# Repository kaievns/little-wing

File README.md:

# Little Wing Keyboard

This my attempt to build a better keyboard for myself.

Think of it as a 32% split bluetooth keyboard merged with the classic MX Ergo trackball

## License

Little Wing Keyboard © 2024 by Kai Evans is licensed under CC BY-SA 4.0

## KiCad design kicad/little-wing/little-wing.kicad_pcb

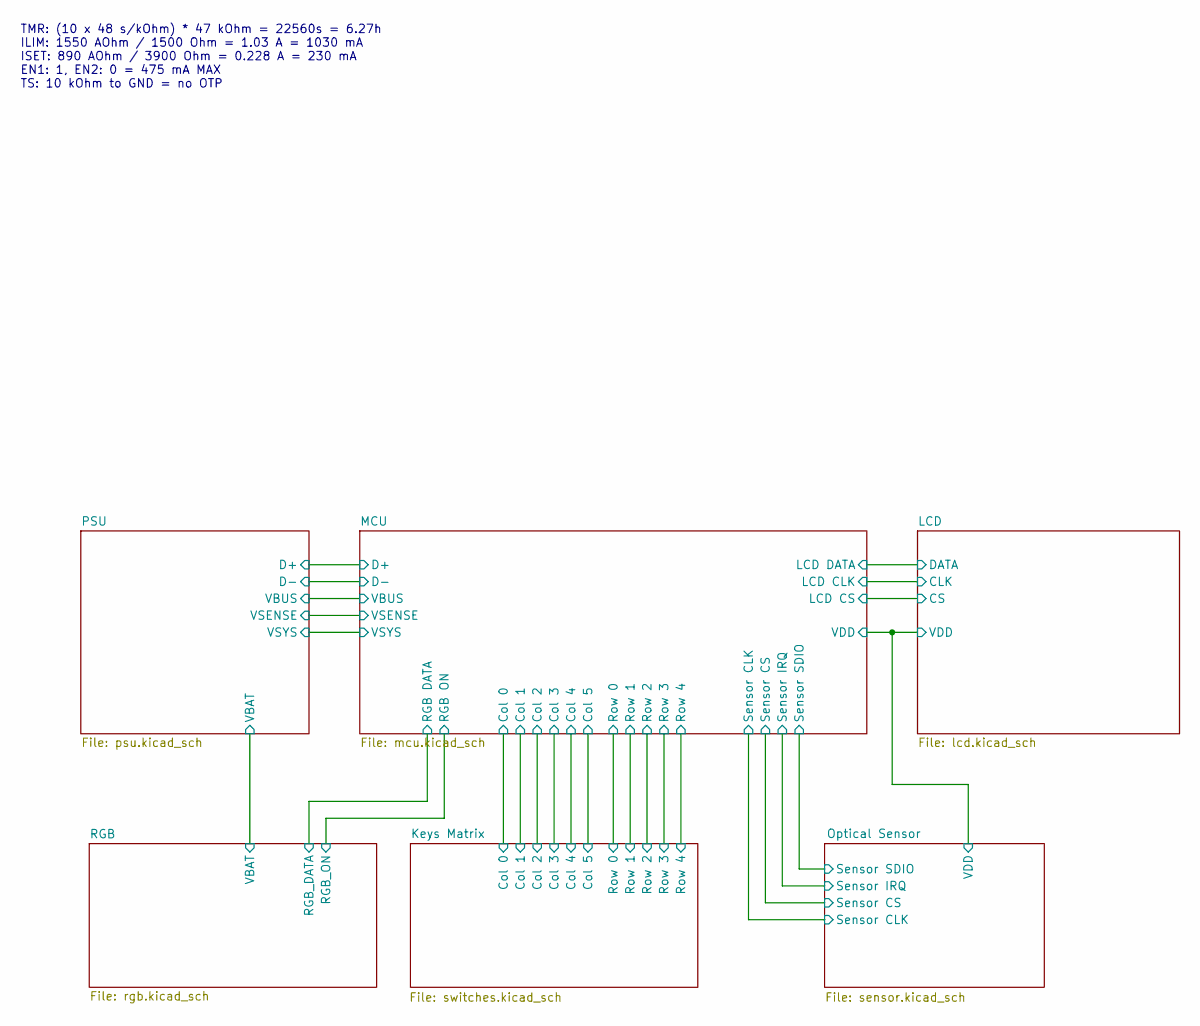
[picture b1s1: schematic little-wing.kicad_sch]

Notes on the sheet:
TMR: (10 x 48 s/kOhm) * 47 kOhm = 22560s = 6.27h ILIM: 1550 AOhm / 1500 Ohm = 1.03 A = 1030 mA ISET: 890 AOhm / 3900 Ohm = 0.228 A = 230 mA EN1: 1, EN2: 0 = 475 mA MAX TS: 10 kOhm to GND = no OTP

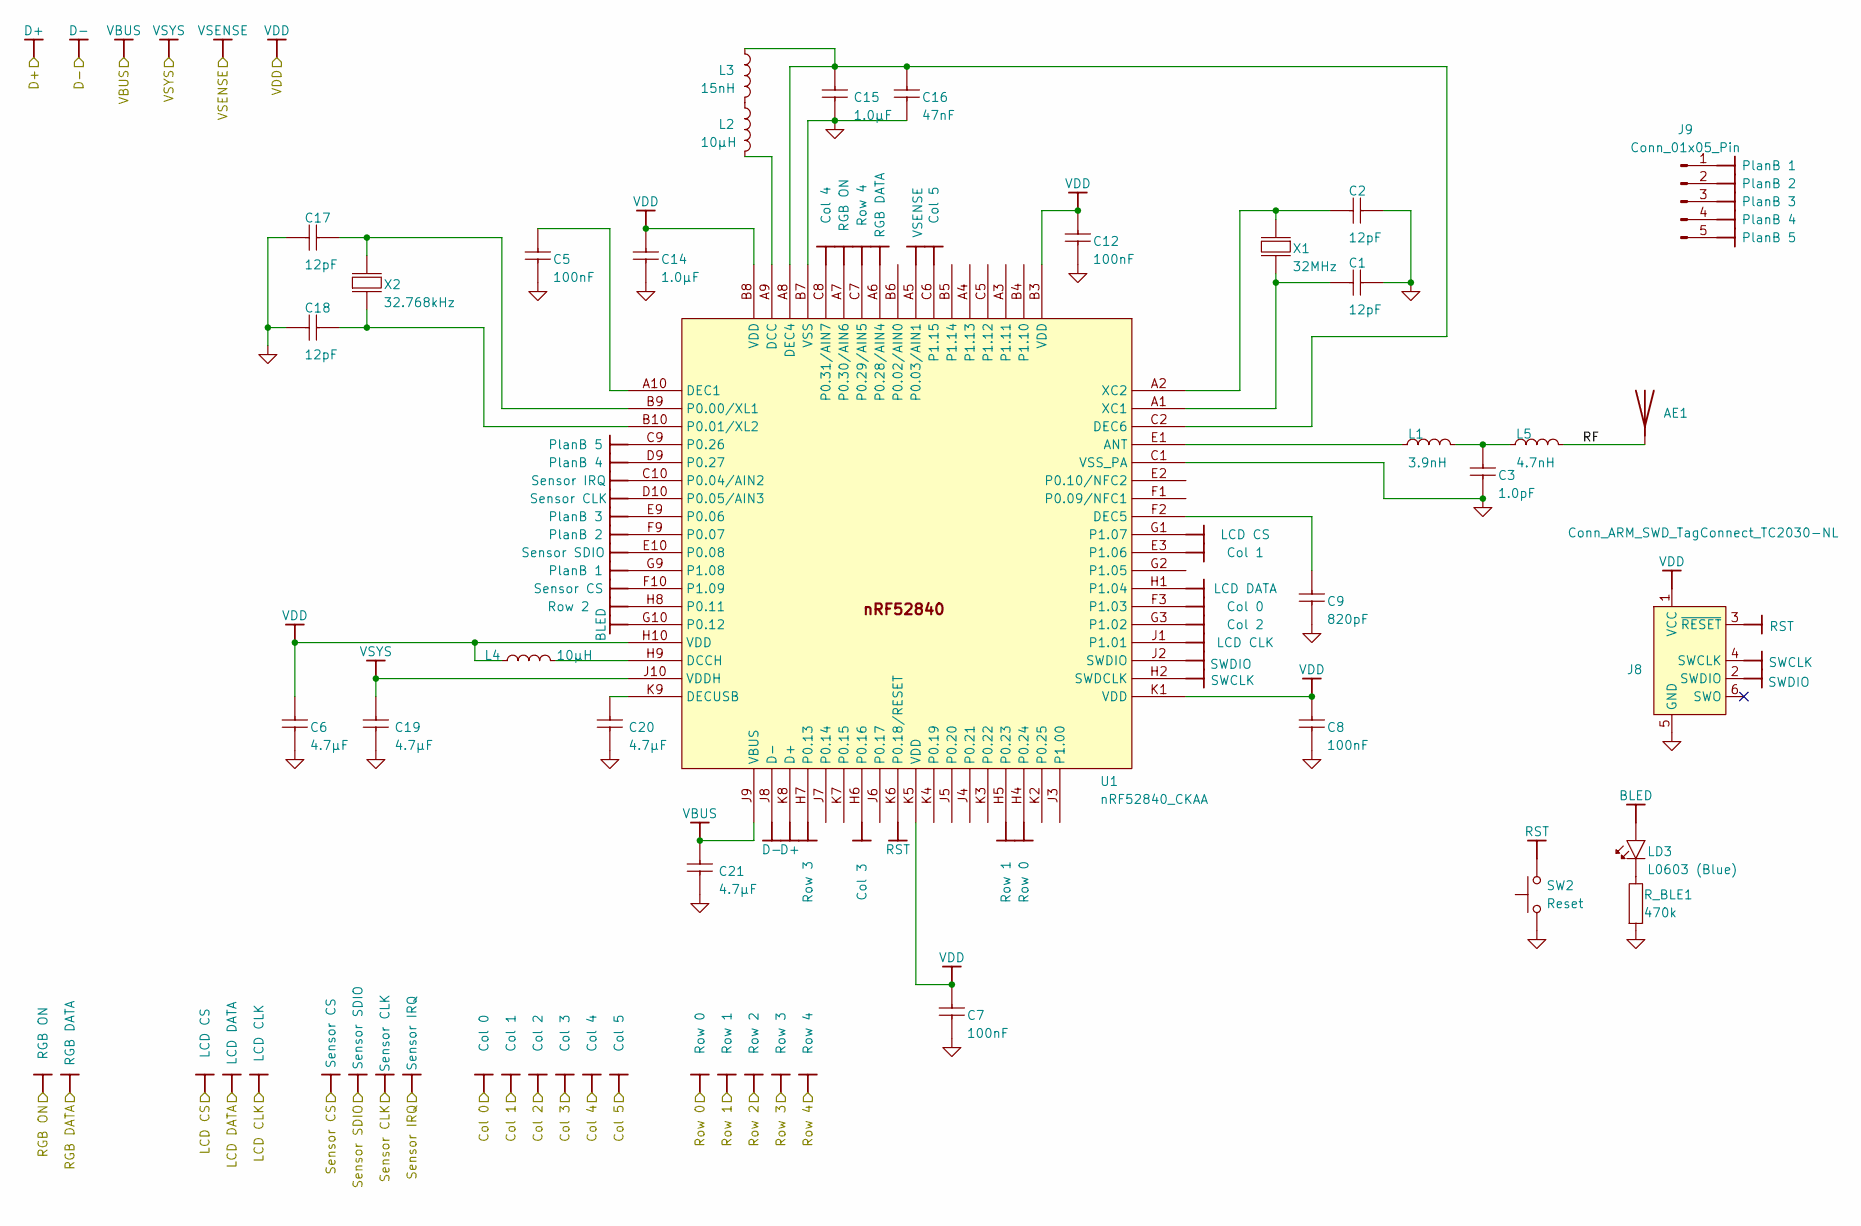
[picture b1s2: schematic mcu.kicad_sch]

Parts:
AE1: 2450AT18A100E; ANT2012LL13R2400A; PARTREV 1.3
C1, C2, C17, C18: 12pF; C_0201_0603Metric; PART NUMBER C0201-12p
C3: 1.0pF; C_0201_0603Metric; PART NUMBER C0201-1.0p
C5, C7, C8: 100nF; C_0201_0603Metric; PART NUMBER C0201-100n
C6, C20: 4.7µF; CAPC1608X06L; PART NUMBER C0603-4µ7-6.3V-X7R
C9: 820pF; C_0201_0603Metric; PART NUMBER C0201-820p
C12: 100nF; CAPC0603X03L_C; PART NUMBER C0201-100n
C14, C15: 1.0µF; CAPC1608X06L; PART NUMBER C0603-1µ0
C16: 47nF; CAPC0603X03L_C; PART NUMBER C0201-47n
C19, C21: 4.7µF; CAPC1608X06L; PART NUMBER C0603-4µ7-10V-X7S
J8: Conn_ARM_SWD_TagConnect_TC2030-NL; Tag-Connect_TC2030-IDC-NL_2x03_P1.27mm_Vertical
J9: Conn_01x05_Pin; JST_SHL_SM05B-SHLS-TF_1x05-1MP_P1.00mm_Horizontal
L1: 3.9nH; INDC0603X03L_C; PART NUMBER L0201-3n9
L2, L4: 10µH; INDC1608X06L; PART NUMBER L0603-10µ
L3: 15nH; INDC1005X04L; PART NUMBER L0402-15n
L5: 4.7nH; INDC0603X03L_C; PART NUMBER L0201-4n7
LD3: L0603 (Blue); LED_0201_0603Metric
R_BLE1: 470k; R_0201_0603Metric
SW2: Reset; SW_SPST_B3U-3000P
U1: nRF52840_CKAA; BGA94C35P10X10_352X356X50; PART NUMBER nRF52840-CKAAD0
X1: 32MHz; Crystal_SMD_1210-4Pin_1.2x1.0mm; PART NUMBER XTAL_SMD2016_32MHz_8pF_General
X2: 32.768kHz; XTAL_ECS32761210TR; PART NUMBER XTAL_SMD2012_32.768kHz_9pF_General

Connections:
/MCU/RF: AE1.1 (A), L5.2
BLED: LD3.2 (A), U1.G10 (P0.12)
Col 0: U1.F3 (P1.03); also elsewhere on the board
Col 1: U1.E3 (P1.06); also elsewhere on the board
Col 2: U1.G3 (P1.02); also elsewhere on the board
Col 3: U1.H6 (P0.16); also elsewhere on the board
Col 4: U1.C8 (P0.31/AIN7); also elsewhere on the board
Col 5: U1.C6 (P1.15); also elsewhere on the board
D+: U1.K8 (D+); also elsewhere on the board
D-: U1.J8 (D-); also elsewhere on the board
LCD CLK: U1.J1 (P1.01); also elsewhere on the board
LCD CS: U1.G1 (P1.07); also elsewhere on the board
LCD DATA: U1.H1 (P1.04); also elsewhere on the board
unnamed: C3.2, L1.2, L5.1
unnamed: L2.1, L3.2
unnamed: LD3.1 (C), R_BLE1.1
unnamed: L1.1, U1.E1 (ANT)
unnamed: L2.2, U1.A9 (DCC)
unnamed: L4.2, U1.H9 (DCCH)
unnamed: C5.1, U1.A10 (DEC1)
unnamed: C15.2, C16.1, L3.1, U1.A8 (DEC4), U1.C2 (DEC6)
unnamed: C9.1, U1.F2 (DEC5)
unnamed: C20.1, U1.K9 (DECUSB)
unnamed: C17.1, U1.B9 (P0.00/XL1), X2.1 (inp)
unnamed: C18.1, U1.B10 (P0.01/XL2), X2.2 (out)
unnamed: C1.1, U1.A1 (XC1), X1.1 (inp)
unnamed: C2.1, U1.A2 (XC2), X1.3 (out)
PlanB 1: J9.1, U1.G9 (P1.08)
PlanB 2: J9.2, U1.F9 (P0.07)
PlanB 3: J9.3, U1.E9 (P0.06)
PlanB 4: J9.4, U1.D9 (P0.27)
PlanB 5: J9.5, U1.C9 (P0.26)
RGB DATA: U1.A6 (P0.28/AIN4); also elsewhere on the board
RGB ON: U1.A7 (P0.30/AIN6); also elsewhere on the board
RST: J8.3 (~RESET), SW2.2, U1.K6 (P0.18/RESET); also elsewhere on the board
Row 0: U1.H4 (P0.24); also elsewhere on the board
Row 1: U1.H5 (P0.23); also elsewhere on the board
Row 2: U1.H8 (P0.11); also elsewhere on the board
Row 3: U1.H7 (P0.13); also elsewhere on the board
Row 4: U1.C7 (P0.29/AIN5); also elsewhere on the board
SWCLK: J8.4 (SWCLK), U1.H2 (SWDCLK)
SWDIO: J8.2 (SWDIO), U1.J2 (SWDIO)
Sensor CLK: U1.D10 (P0.05/AIN3); also elsewhere on the board
Sensor CS: U1.F10 (P1.09); also elsewhere on the board
Sensor IRQ: U1.C10 (P0.04/AIN2); also elsewhere on the board
Sensor SDIO: U1.E10 (P0.08); also elsewhere on the board
VBUS: C21.1, U1.J9 (VBUS); also elsewhere on the board
VDD: C6.1, C7.1, C8.1, C12.1, C14.1, J8.1 (VCC), L4.1, U1.B3 (VDD), U1.B8 (VDD), U1.H10 (VDD), U1.K1 (VDD), U1.K5 (VDD); also elsewhere on the board
VSENSE: U1.A5 (P0.03/AIN1); also elsewhere on the board
VSYS: C19.1, U1.J10 (VDDH); also elsewhere on the board

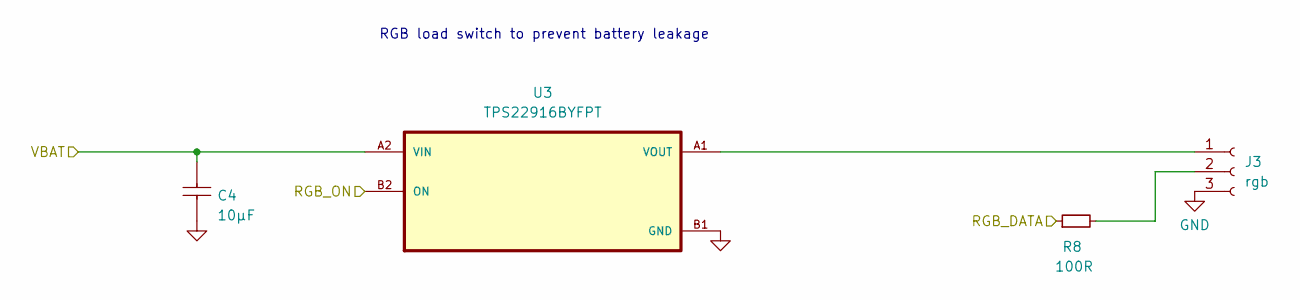
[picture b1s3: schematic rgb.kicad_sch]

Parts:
C4: 10µF; CAPC1608X06L; PART NUMBER C0603-1µ0
J3: rgb; JST_SH_SM03B-SRSS-TB_1x03-1MP_P1.00mm_Horizontal
R8: 100R; R_0201_0603Metric
U3: TPS22916BYFPT; BGA4C40P2X2_77X77X50

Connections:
unnamed: J3.1, U3.A1 (VOUT)
unnamed: J3.2, R8.2
RGB DATA: R8.1; also elsewhere on the board
RGB ON: U3.B2 (ON); also elsewhere on the board
VBAT: C4.2, U3.A2 (VIN); also elsewhere on the board

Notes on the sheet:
RGB load switch to prevent battery leakage

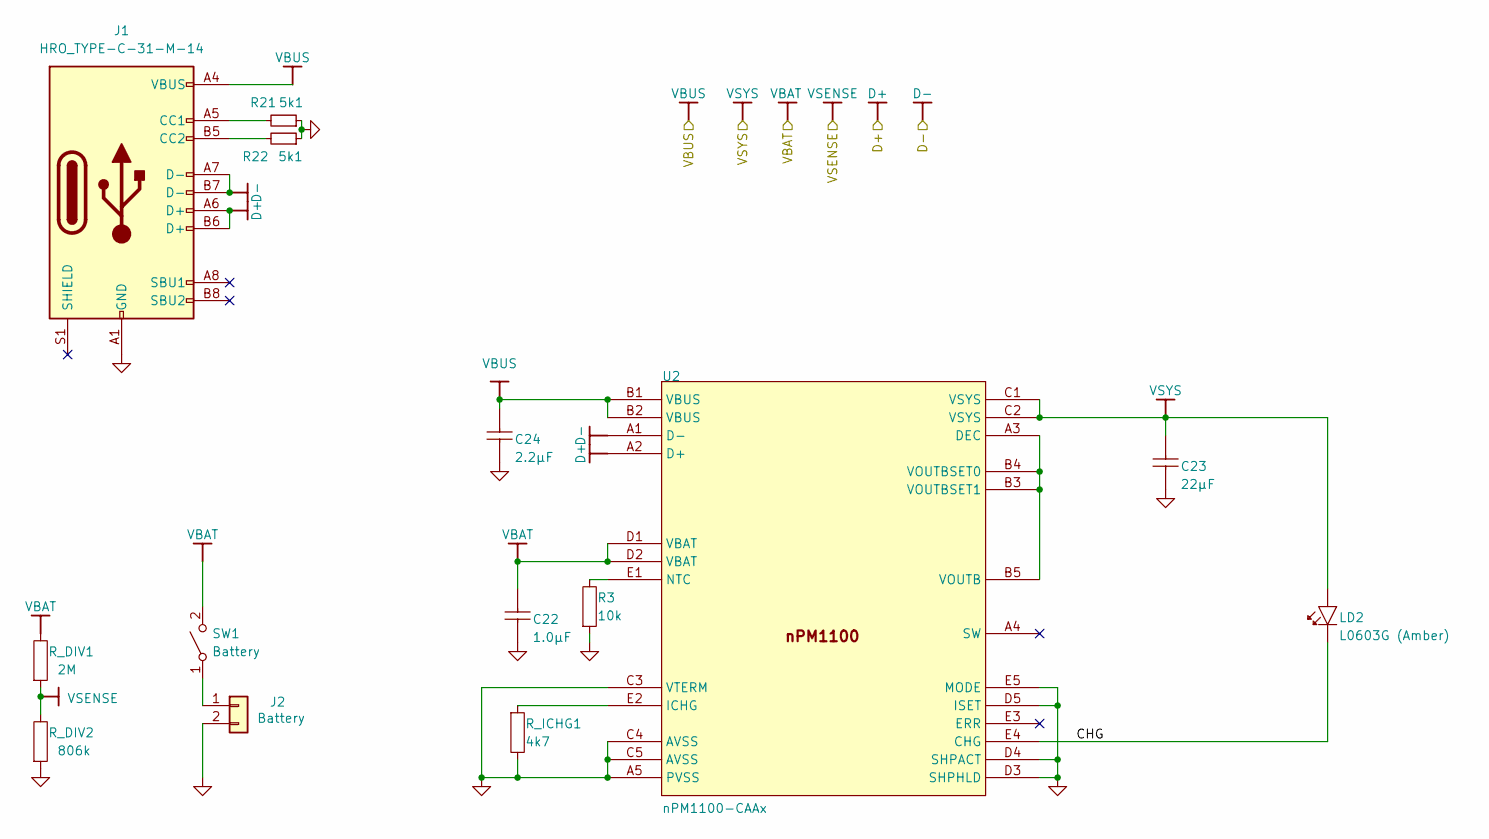
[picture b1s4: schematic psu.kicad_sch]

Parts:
C22: 1.0µF; C_0201_0603Metric
C23: 22µF; CAPC1608X06L
C24: 2.2µF; CAPC1608X06L
J1: HRO_TYPE-C-31-M-14; USB_C_Receptacle_HRO_TYPE-C-31-M-12
J2: Battery; JST_SH_SM02B-SRSS-TB_1x02-1MP_P1.00mm_Horizontal
LD2: L0603G (Amber); LED_0201_0603Metric
R3: 10k; R_0201_0603Metric
R21, R22: 5k1; R_0201_0603Metric
R_DIV1: 2M; R_0201_0603Metric
R_DIV2: 806k; R_0201_0603Metric
R_ICHG1: 4k7; R_0201_0603Metric
SW1: Battery; Switch_MSK12C02
U2: nPM1100-CAAx; BGA25C40P5X5_200X200X50

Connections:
/PSU/CHG: LD2.1 (C), U2.E4 (CHG)
D+: J1.A6 (D+), J1.B6 (D+), U2.A2 (D+); also elsewhere on the board
D-: J1.A7 (D-), J1.B7 (D-), U2.A1 (D-); also elsewhere on the board
unnamed: J1.A5 (CC1), R21.2
unnamed: J1.B5 (CC2), R22.2
unnamed 20: J2.1, SW1.1 (A); also elsewhere on the board
unnamed: U2.A3 (DEC), U2.B3 (VOUTBSET1), U2.B4 (VOUTBSET0), U2.B5 (VOUTB)
unnamed: R_ICHG1.2, U2.E2 (ICHG)
unnamed: R3.1, U2.E1 (NTC)
VBAT: C22.2, R_DIV1.1, SW1.2 (B), U2.D1 (VBAT), U2.D2 (VBAT); also elsewhere on the board
VBUS: C24.2, J1.A4 (VBUS), J1.A9 (VBUS), J1.B4 (VBUS), J1.B9 (VBUS), U2.B1 (VBUS), U2.B2 (VBUS); also elsewhere on the board
VSENSE: R_DIV1.2, R_DIV2.1; also elsewhere on the board
VSYS: C23.2, LD2.2 (A), U2.C1 (VSYS), U2.C2 (VSYS); also elsewhere on the board

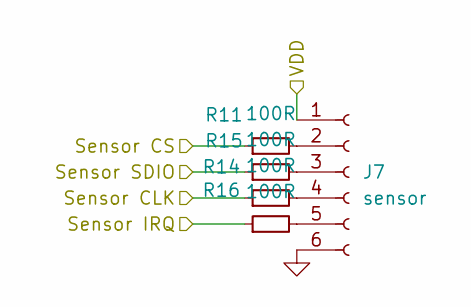
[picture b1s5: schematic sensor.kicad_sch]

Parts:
J7: sensor; JST_SH_SM06B-SRSS-TB_1x06-1MP_P1.00mm_Horizontal
R11, R14, R15, R16: 100R; R_0201_0603Metric

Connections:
unnamed: J7.2, R11.2
unnamed: J7.3, R14.2
unnamed: J7.4, R15.2
unnamed: J7.5, R16.2
Sensor CLK: R15.1; also elsewhere on the board
Sensor CS: R11.1; also elsewhere on the board
Sensor IRQ: R16.1; also elsewhere on the board
Sensor SDIO: R14.1; also elsewhere on the board
VDD: J7.1; also elsewhere on the board

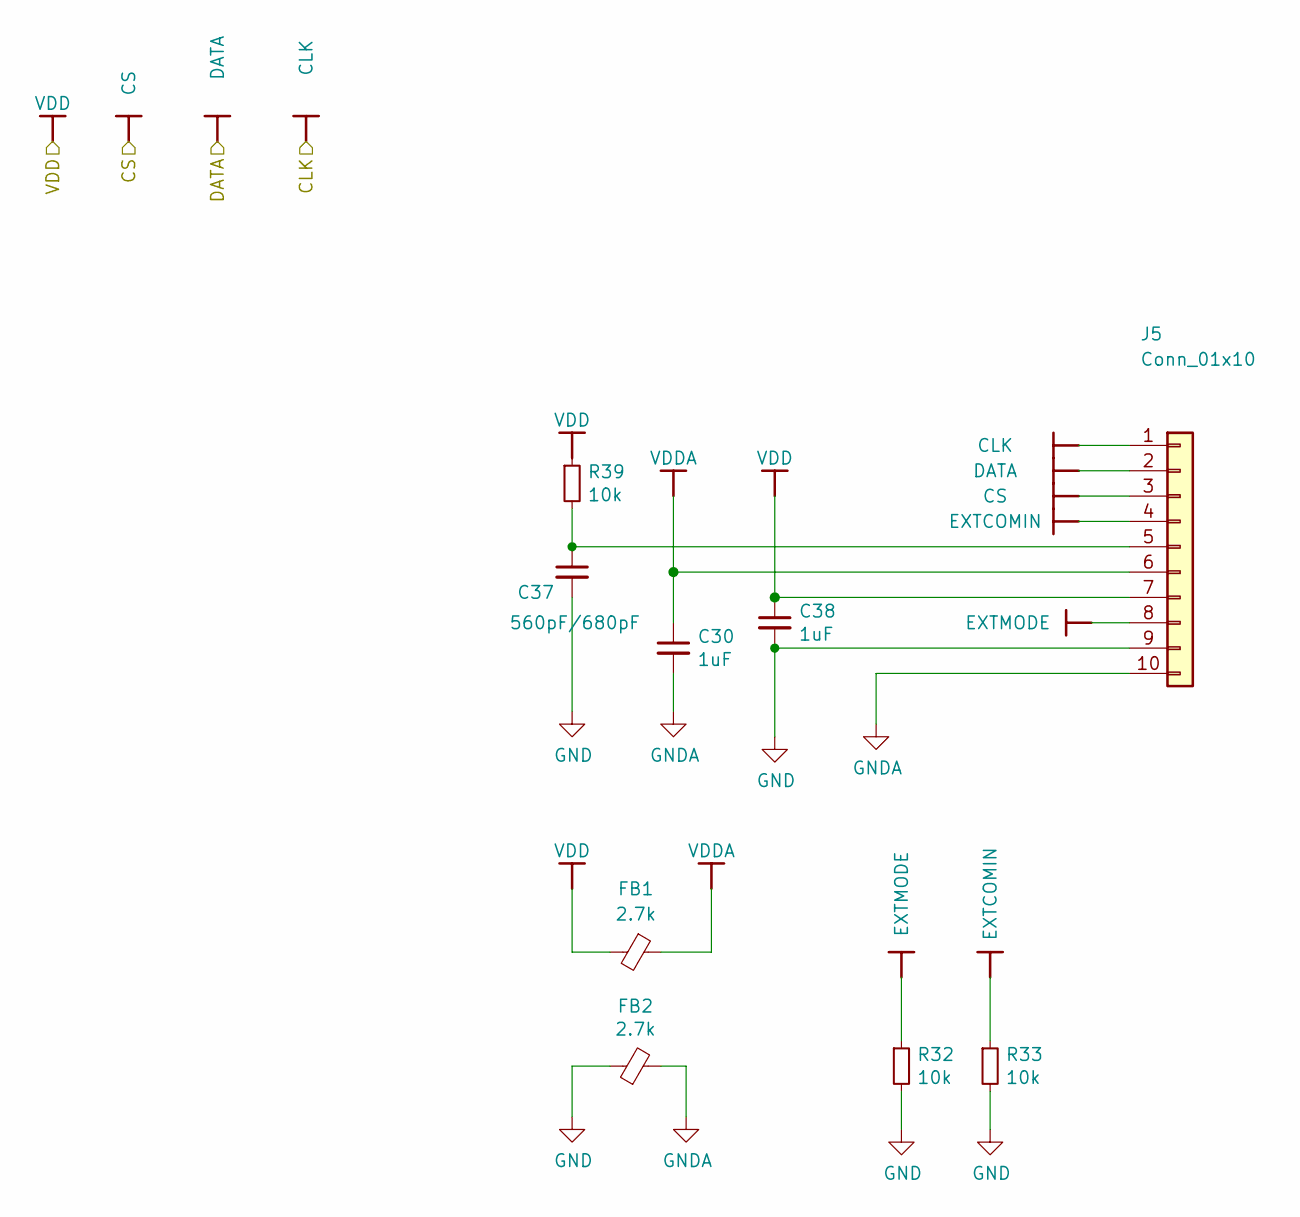
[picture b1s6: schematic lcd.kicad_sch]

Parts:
C30, C38: 1uF; C_0201_0603Metric; LCSC C15849
C37: 560pF/680pF; C_0201_0603Metric; LCSC C84721
FB1, FB2: 2.7k; R_0402_1005Metric; LCSC C1017
J5: Conn_01x10; CONN10x1_FH34SRJ-10S-0.5SH50_HIR; LCSC C506791
R32, R33, R39: 10k; R_0201_0603Metric; LCSC C25804

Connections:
EXTCOMIN: J5.4, R33.1
EXTMODE: J5.8, R32.1
GNDA: C30.2, FB2.2, J5.10
LCD CLK: J5.1; also elsewhere on the board
LCD CS: J5.3; also elsewhere on the board
LCD DATA: J5.2; also elsewhere on the board
unnamed: C37.1, J5.5, R39.2
VDD: C38.1, FB1.2, J5.7, R39.1; also elsewhere on the board
VDDA: C30.1, FB1.1, J5.6

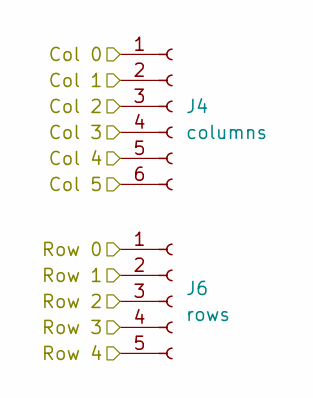
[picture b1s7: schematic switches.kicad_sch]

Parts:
J4: columns; JST_SH_SM06B-SRSS-TB_1x06-1MP_P1.00mm_Horizontal
J6: rows; JST_SH_SM05B-SRSS-TB_1x05-1MP_P1.00mm_Horizontal

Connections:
Col 0: J4.1; also elsewhere on the board
Col 1: J4.2; also elsewhere on the board
Col 2: J4.3; also elsewhere on the board
Col 3: J4.4; also elsewhere on the board
Col 4: J4.5; also elsewhere on the board
Col 5: J4.6; also elsewhere on the board
Row 0: J6.1; also elsewhere on the board
Row 1: J6.2; also elsewhere on the board
Row 2: J6.3; also elsewhere on the board
Row 3: J6.4; also elsewhere on the board
Row 4: J6.5; also elsewhere on the board

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
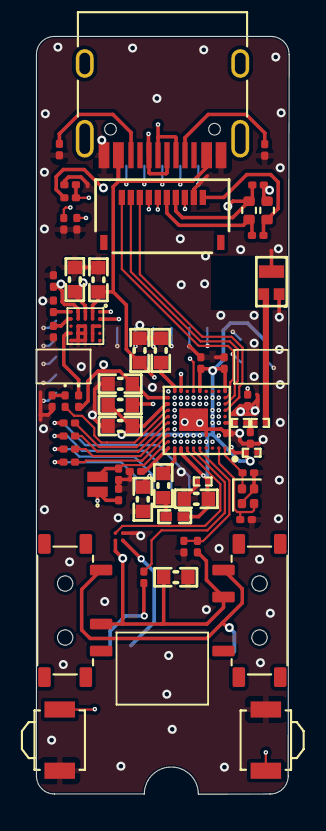
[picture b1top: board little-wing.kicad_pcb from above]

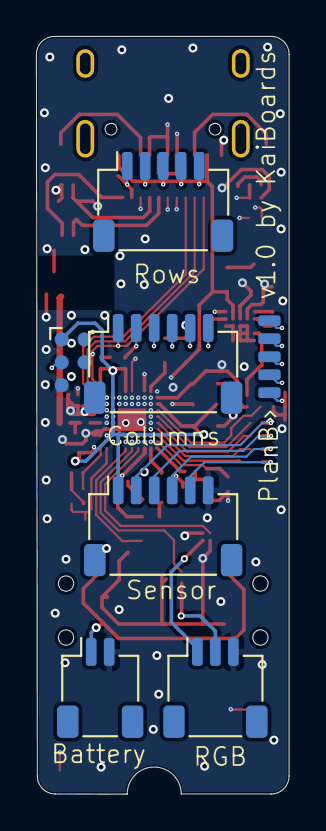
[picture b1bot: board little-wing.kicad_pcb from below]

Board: 4 copper layers, 14.0 x 42.1 mm, 67 parts (7 on the bottom side), 70 nets.

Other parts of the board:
SW1#2: Battery; Switch_MSK12C02
SW2#2: Reset; SW_SPST_B3U-3000P

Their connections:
unnamed 20: SW1#2.1 (A); also elsewhere on the board
RST: SW2#2.2; also elsewhere on the board
VBAT: SW1#2.2 (B); also elsewhere on the board

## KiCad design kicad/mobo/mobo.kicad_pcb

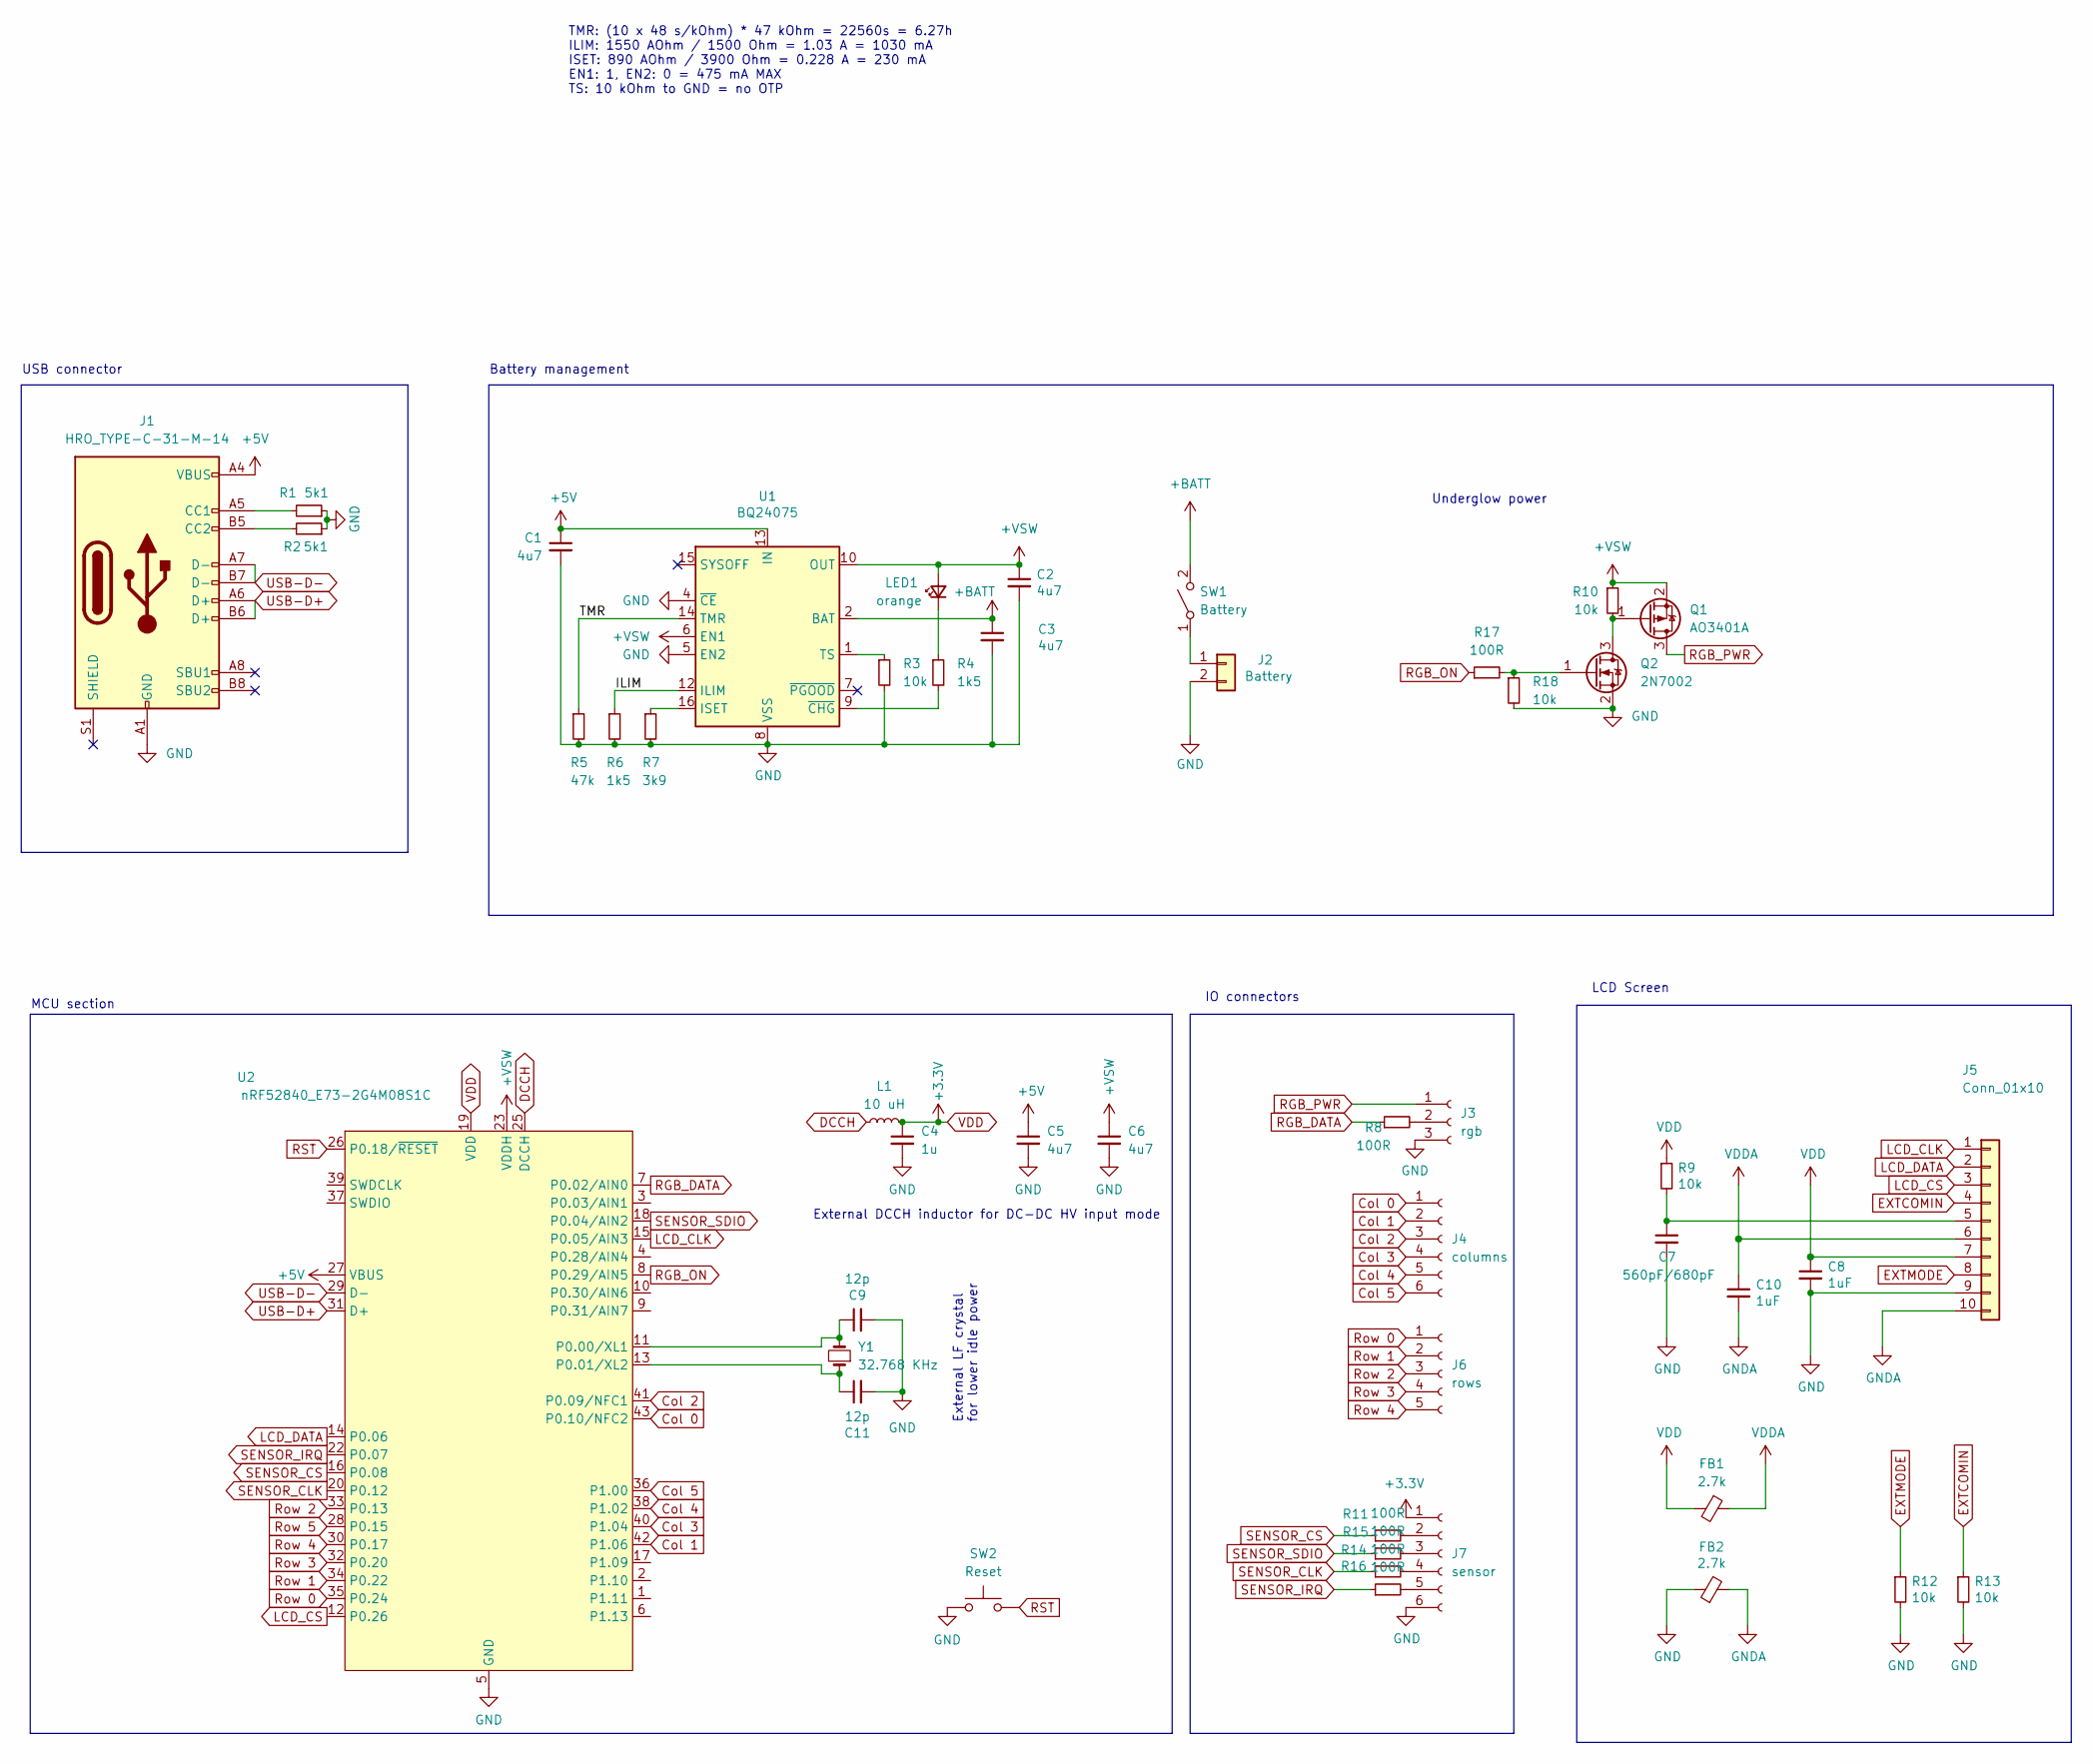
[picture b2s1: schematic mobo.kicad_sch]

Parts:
C1, C2, C3, C5, C6: 4u7; C_0402_1005Metric
C4: 1u; C_0402_1005Metric
C7: 560pF/680pF; C_0603_1608Metric_Pad1.08x0.95mm_HandSolder; LCSC C84721
C8, C10: 1uF; C_0603_1608Metric_Pad1.08x0.95mm_HandSolder; LCSC C15849
C9, C11: 12p; C_0402_1005Metric
FB1, FB2: 2.7k; R_0805_2012Metric_Pad1.20x1.40mm_HandSolder; LCSC C1017
J1: HRO_TYPE-C-31-M-14; USB_C_Receptacle_HRO_TYPE-C-31-M-12
J2: Battery; JST_SH_SM02B-SRSS-TB_1x02-1MP_P1.00mm_Horizontal
J3: rgb; JST_SH_SM03B-SRSS-TB_1x03-1MP_P1.00mm_Horizontal
J4: columns; JST_SH_SM06B-SRSS-TB_1x06-1MP_P1.00mm_Horizontal
J5: Conn_01x10; Hirose_FH12-10S-0.5SH_1x10-1MP_P0.50mm_Horizontal; LCSC C506791
J6: rows; JST_SH_SM05B-SRSS-TB_1x05-1MP_P1.00mm_Horizontal
J7: sensor; JST_SH_SM06B-SRSS-TB_1x06-1MP_P1.00mm_Horizontal
L1: 10 uH; L_0603_1608Metric; LCSC C92982
LED1: orange; LED_0402_1005Metric
Q1: AO3401A; SOT-23
Q2: 2N7002; SOT-23
R1, R2: 5k1; R_0402_1005Metric
R3, R10, R18: 10k; R_0402_1005Metric
R4, R6: 1k5; R_0402_1005Metric
R5: 47k; R_0402_1005Metric
R7: 3k9; R_0402_1005Metric
R8, R11, R14, R15, R16, R17: 100R; R_0402_1005Metric
R9, R12, R13: 10k; R_0603_1608Metric_Pad0.98x0.95mm_HandSolder; LCSC C25804
SW1: Battery
SW2: Reset; SW_SPST_B3U-1000P
U1: BQ24075; VQFN-16-1EP_3x3mm_P0.5mm_EP1.6x1.6mm
U2: nRF52840_E73-2G4M08S1C; E73-2G4M08S1C; LCSC C356849
Y1: 32.768 KHz; Crystal_SMD_2012-2Pin_2.0x1.2mm; LCSC C55208

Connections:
+5V: C1.1, C5.1, J1.A4 (VBUS), J1.A9 (VBUS), J1.B4 (VBUS), J1.B9 (VBUS), U1.13 (IN), U2.27 (VBUS)
+BATT: C3.1, SW1.2 (B), U1.2 (BAT), U1.3 (BAT); also elsewhere on the board
+VSW: C2.1, C6.1, LED1.2 (A), Q1.2 (S), R10.1, U1.6 (EN1), U1.10 (OUT), U1.11 (OUT), U2.23 (VDDH)
/ILIM: R6.1, U1.12 (ILIM)
/TMR: R5.1, U1.14 (TMR)
Col 0: J4.1, U2.43 (P0.10/NFC2)
Col 1: J4.2, U2.42 (P1.06)
Col 2: J4.3, U2.41 (P0.09/NFC1)
Col 3: J4.4, U2.40 (P1.04)
Col 4: J4.5, U2.38 (P1.02)
Col 5: J4.6, U2.36 (P1.00)
DCCH: L1.1, U2.25 (DCCH)
EXTCOMIN: J5.4, R13.1
EXTMODE: J5.8, R12.1
GND: C1.2, C2.2, C3.2, C4.2, C5.2, C6.2, C7.2, C8.2, C9.2, C11.2, FB2.1, J1.A1 (GND), J1.A12 (GND), J1.B1 (GND), J1.B12 (GND), J2.2, J3.3, J5.9, J7.6, Q2.2 (S), R1.1, R2.1, R3.2, R5.2, R6.2, R7.2, R12.2, R13.2, R18.2, SW2.1, U1.4 (~CE), U1.5 (EN2), U1.8 (VSS), U1.17 (VSS), U2.5 (GND), U2.21 (GND), U2.24 (GND); also elsewhere on the board
GNDA: C10.2, FB2.2, J5.10
LCD_CLK: J5.1, U2.15 (P0.05/AIN3)
LCD_CS: J5.3, U2.12 (P0.26)
LCD_DATA: J5.2, U2.14 (P0.06)
unnamed: J1.A5 (CC1), R1.2
unnamed: J1.B5 (CC2), R2.2
unnamed 21: J2.1, SW1.1 (A); also elsewhere on the board
unnamed: J3.2, R8.2
unnamed: C7.1, J5.5, R9.2
unnamed: J7.2, R11.2
unnamed: J7.3, R14.2
unnamed: J7.4, R15.2
unnamed: J7.5, R16.2
unnamed: LED1.1 (K), R4.1
unnamed: Q1.1 (G), Q2.3 (D), R10.2
unnamed: Q2.1 (G), R17.2, R18.1
unnamed: R7.1, U1.16 (ISET)
unnamed: R3.1, U1.1 (TS)
unnamed: R4.2, U1.9 (~CHG)
unnamed: C9.1, U2.11 (P0.00/XL1), Y1.2
unnamed: C11.1, U2.13 (P0.01/XL2), Y1.1
RGB_DATA: R8.1, U2.7 (P0.02/AIN0)
RGB_ON: R17.1, U2.8 (P0.29/AIN5)
RGB_PWR: J3.1, Q1.3 (D)
RST: SW2.2, U2.26 (P0.18/~RESET); also elsewhere on the board
Row 0: J6.1, U2.35 (P0.24)
Row 1: J6.2, U2.34 (P0.22)
Row 2: J6.3, U2.33 (P0.13)
Row 3: J6.4, U2.32 (P0.20)
Row 4: J6.5, U2.30 (P0.17)
Row 5: U2.28 (P0.15)
SENSOR_CLK: R15.1, U2.20 (P0.12)
SENSOR_CS: R11.1, U2.16 (P0.08)
SENSOR_IRQ: R16.1, U2.22 (P0.07)
SENSOR_SDIO: R14.1, U2.18 (P0.04/AIN2)
USB-D+: J1.A6 (D+), J1.B6 (D+), U2.31 (D+)
USB-D-: J1.A7 (D-), J1.B7 (D-), U2.29 (D-)
VDD: C4.1, C8.1, FB1.2, J5.7, J7.1, L1.2, R9.1, U2.19 (VDD)
VDDA: C10.1, FB1.1, J5.6

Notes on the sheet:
Battery management
External LF crystal for lower idle power
MCU section
USB connector
IO connectors
TMR: (10 x 48 s/kOhm) * 47 kOhm = 22560s = 6.27h ILIM: 1550 AOhm / 1500 Ohm = 1.03 A = 1030 mA ISET: 890 AOhm / 3900 Ohm = 0.228 A = 230 mA EN1: 1, EN2: 0 = 475 mA MAX TS: 10 kOhm to GND = no OTP
LCD Screen
External DCCH inductor for DC-DC HV input mode
Underglow power

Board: 4 copper layers, 49 parts (6 on the bottom side), 53 nets, no tracks yet.

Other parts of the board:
SW1#2: Battery; Switch_MSK12C02
SW2#2: Reset; SW_SPST_B3U-3000P-B

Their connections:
+BATT: SW1#2.2 (B); also elsewhere on the board
GND: SW2#2.1; also elsewhere on the board
unnamed 21: SW1#2.1 (A); also elsewhere on the board
RST: SW2#2.2; also elsewhere on the board

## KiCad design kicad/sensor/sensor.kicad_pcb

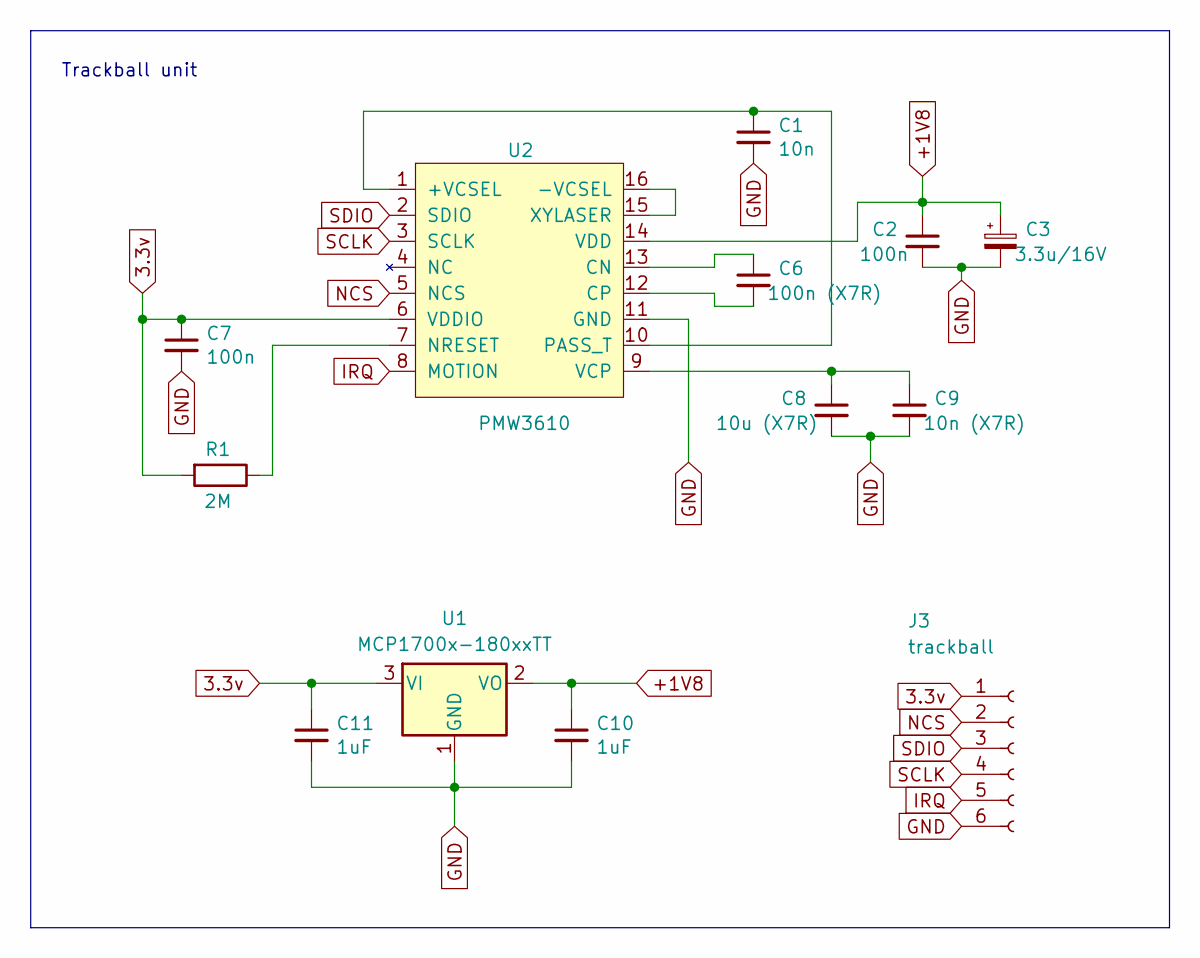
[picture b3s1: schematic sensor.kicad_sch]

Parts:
C1: 10n; C_0603_1608Metric; LCSC C19666
C2, C7: 100n; C_0603_1608Metric; LCSC C19666
C3: 3.3u/16V; C_0603_1608Metric; LCSC C19666
C6: 100n (X7R); C_0603_1608Metric; LCSC C19666
C8: 10u (X7R); C_0603_1608Metric; LCSC C19666
C9: 10n (X7R); C_0603_1608Metric; LCSC C19666
C10, C11: 1uF; C_0603_1608Metric; LCSC C15849
J3: trackball; Wuerth_WR-WTB_64800611622_1x06_P1.50mm_Vertical
R1: 2M; R_0603_1608Metric
U1: MCP1700x-180xxTT; SOT-23
U2: PMW3610

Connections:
3.3v: C7.1, C11.1, J3.1, R1.2, U1.3 (VI), U2.6 (VDDIO)
+1V8: C2.1, C3.1, C10.1, U1.2 (VO), U2.14 (VDD)
GND: C1.2, C2.2, C3.2, C7.2, C8.2, C9.2, C10.2, C11.2, J3.6, U1.1 (GND), U2.11 (GND)
IRQ: J3.5, U2.8 (MOTION)
NCS: J3.2, U2.5 (NCS)
unnamed: C1.1, U2.1 (+VCSEL), U2.10 (PASS_T)
unnamed: U2.15 (XYLASER), U2.16 (-VCSEL)
unnamed: C6.1, U2.13 (CN)
unnamed: C6.2, U2.12 (CP)
unnamed: R1.1, U2.7 (NRESET)
unnamed: C8.1, C9.1, U2.9 (VCP)
SCLK: J3.4, U2.3 (SCLK)
SDIO: J3.3, U2.2 (SDIO)

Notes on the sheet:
Trackball unit

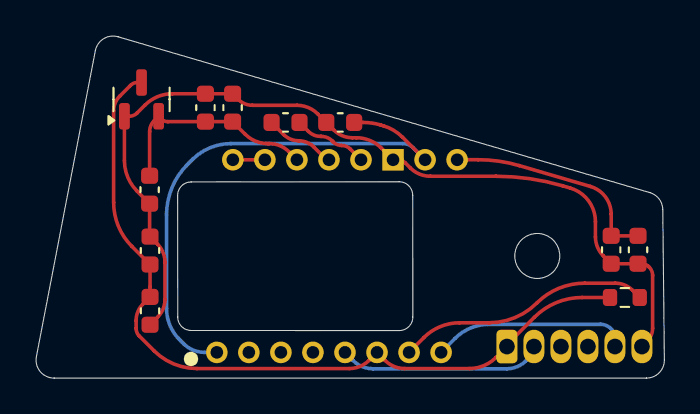
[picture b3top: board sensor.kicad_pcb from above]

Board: 4 copper layers, 34.9 x 19.0 mm, 13 parts (0 on the bottom side), 13 nets.

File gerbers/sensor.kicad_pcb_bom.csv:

Designator,Quantity,Value,Footprint,Package,MPN,DNP,Mount_Type,LCSC,Description
C1,1,10n,C_0603_1608Metric,,,,smt,C19666,
"C10, C11",2,1uF,C_0603_1608Metric,,,,smt,C15849,
"C2, C7",2,100n,C_0603_1608Metric,,,,smt,C19666,
C3,1,3.3u/16V,C_0603_1608Metric,,,,smt,C19666,"Polarized capacitor, small symbol"
C6,1,100n (X7R),C_0603_1608Metric,,,,smt,C19666,
C8,1,10u (X7R),C_0603_1608Metric,,,,smt,C19666,
C9,1,10n (X7R),C_0603_1608Metric,,,,smt,C19666,
J3,1,trackball,Wuerth_WR-WTB_64800611622_1x06_P1.50mm_Vertical,,,,tht,,"Generic connector, single row, 01x06, script generated"
R1,1,2M,R_0603_1608Metric,,,,smt,,
U1,1,MCP1700x-180xxTT,SOT-23,,,,smt,,"250mA Low Quiscent Current LDO, 1.8V output, SOT-23"
U2,1,PMW3610,PMW3610,,,,tht,,

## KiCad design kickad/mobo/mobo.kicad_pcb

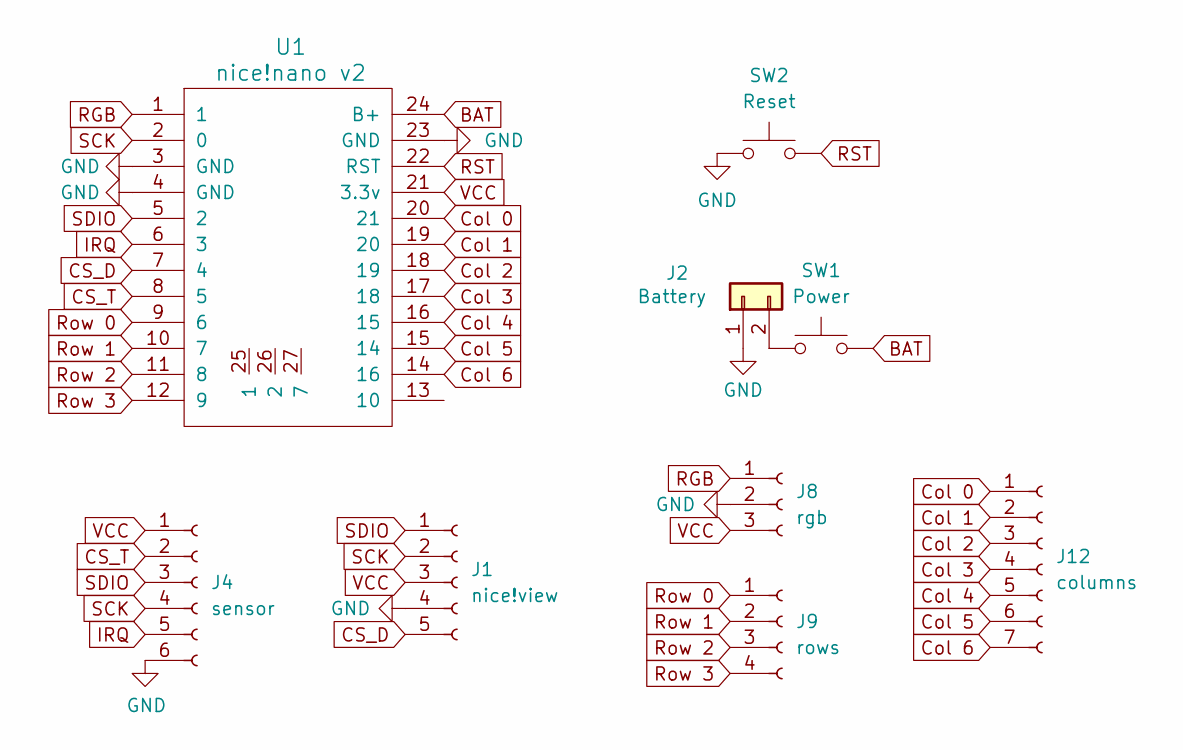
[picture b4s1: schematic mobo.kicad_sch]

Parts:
J1: nice!view; PinHeader_1x05_P2.54mm_Vertical
J2: Battery; JST_ZH_S2B-ZR-SM4A-TF_1x02-1MP_P1.50mm_Horizontal
J4: sensor; Wuerth_WR-WTB_64800611622_1x06_P1.50mm_Vertical
J8: rgb; Wuerth_WR-WTB_64800311622_1x03_P1.50mm_Vertical
J9: rows; Wuerth_WR-WTB_64800411622_1x04_P1.50mm_Vertical
J12: columns; Wuerth_WR-WTB_64800711622_1x07_P1.50mm_Vertical
SW1: Power; SW_SPDT_PCM12
SW2: Reset; SW_SPST_B3U-1000P
U1: nice!nano v2; Nice_Nano_V2_Flipped

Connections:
BAT: SW1.2, U1.24 (B+)
CS_D: J1.5, U1.7 (4)
CS_T: J4.2, U1.8 (5)
Col 0: J12.1, U1.20 (21)
Col 1: J12.2, U1.19 (20)
Col 2: J12.3, U1.18 (19)
Col 3: J12.4, U1.17 (18)
Col 4: J12.5, U1.16 (15)
Col 5: J12.6, U1.15 (14)
Col 6: J12.7, U1.14 (16)
GND: J1.4, J2.1, J4.6, J8.2, SW2.1, U1.3 (GND), U1.4 (GND), U1.23 (GND)
IRQ: J4.5, U1.6 (3)
unnamed: J2.2, SW1.1
RGB: J8.1, U1.1
RST: SW2.2, U1.22 (RST)
Row 0: J9.1, U1.9 (6)
Row 1: J9.2, U1.10 (7)
Row 2: J9.3, U1.11 (8)
Row 3: J9.4, U1.12 (9)
SCK: J1.2, J4.4, U1.2 (0)
SDIO: J1.1, J4.3, U1.5 (2)
VCC: J1.3, J4.1, J8.3, U1.21 (3.3v)
